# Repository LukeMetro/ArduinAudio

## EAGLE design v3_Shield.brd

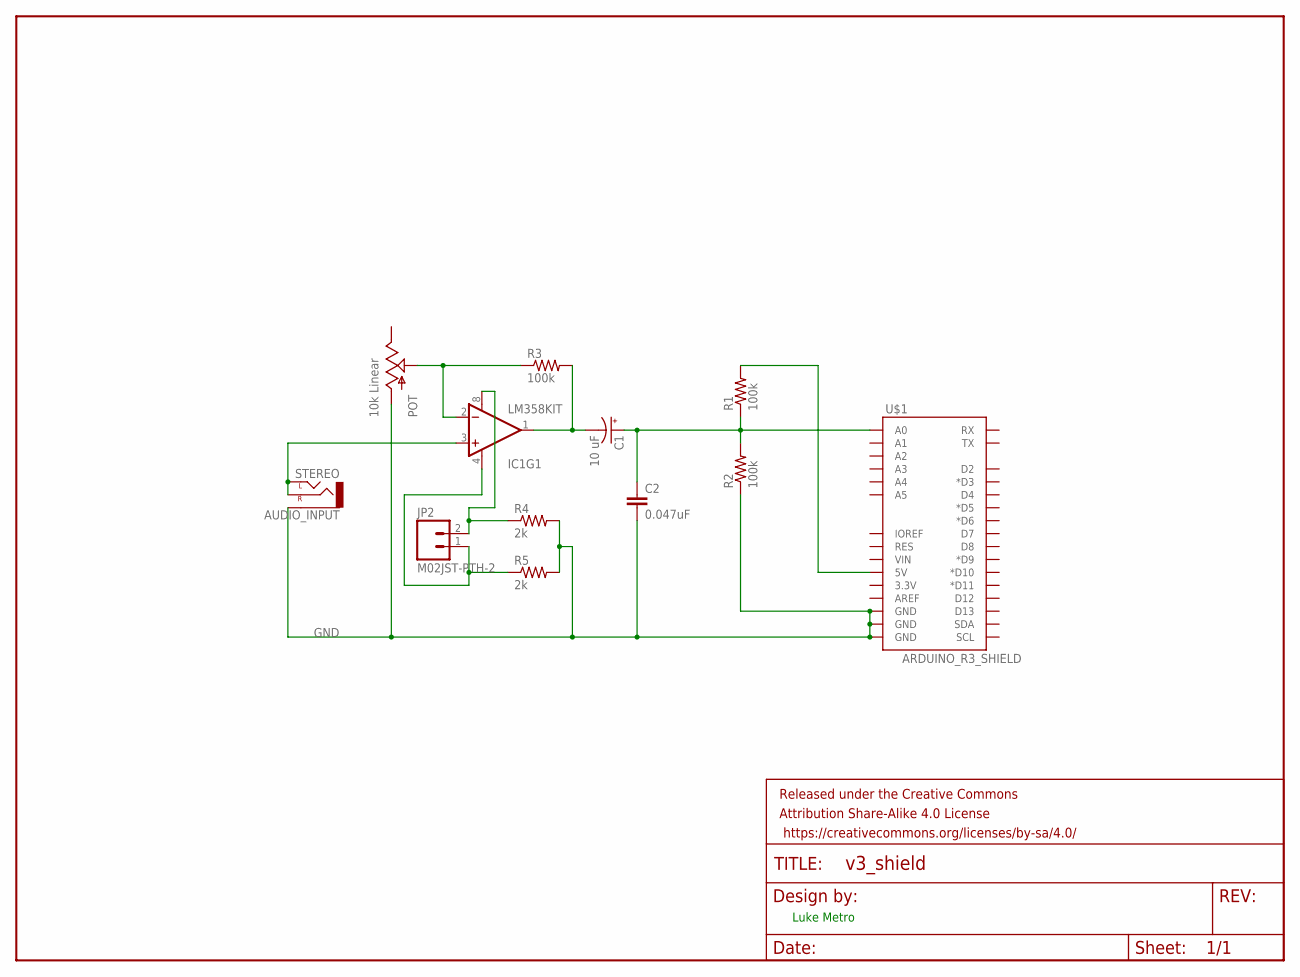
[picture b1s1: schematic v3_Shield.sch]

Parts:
AUDIO_INPUT: STEREO; AUDIO-JACK
C1: 10 uF; EIA6032
C2: 0.047uF; 0402-CAP
FRAME1: FRAME-LETTER; CREATIVE_COMMONS
IC1: LM358KIT; DIP08-KIT
JP2: M02JST-PTH-2; JST-2-PTH
POT: 10k Linear; ALPS_POT
R1, R2, R3: 100k; 0805-THM
R4, R5: 2k; 0805-THM
U$1: ARDUINO_R3_SHIELD; UNO_R3_SHIELD

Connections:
2.5V_OFFSET_HOT: R1.2, U$1.5V
GND: AUDIO_INPUT.SLEEVE, C2.2, POT.P$3 (A), R2.1, R4.2, R5.2, U$1.GND@0 (GND), U$1.GND@1 (GND), U$1.GND@2 (GND)
OPAMP_IN: AUDIO_INPUT.RING (RIGHT), AUDIO_INPUT.TIP (LEFT), IC1.3 (+IN)
OPAMP_INVERTING_INPUT: IC1.2 (-IN), POT.P$2 (S), R3.1
OPAMP_OUT: C1.P$2 (-), IC1.1 (OUT), R3.2
OPAMP_PWR_COLD: IC1.4 (V-), JP2.1, R5.1
OPAMP_PWR_HOT: IC1.8 (V+), JP2.2, R4.1
OUTPUT_SIGNAL: C1.P$1 (+), C2.1, R1.1, R2.2, U$1.A0

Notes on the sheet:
Luke Metro

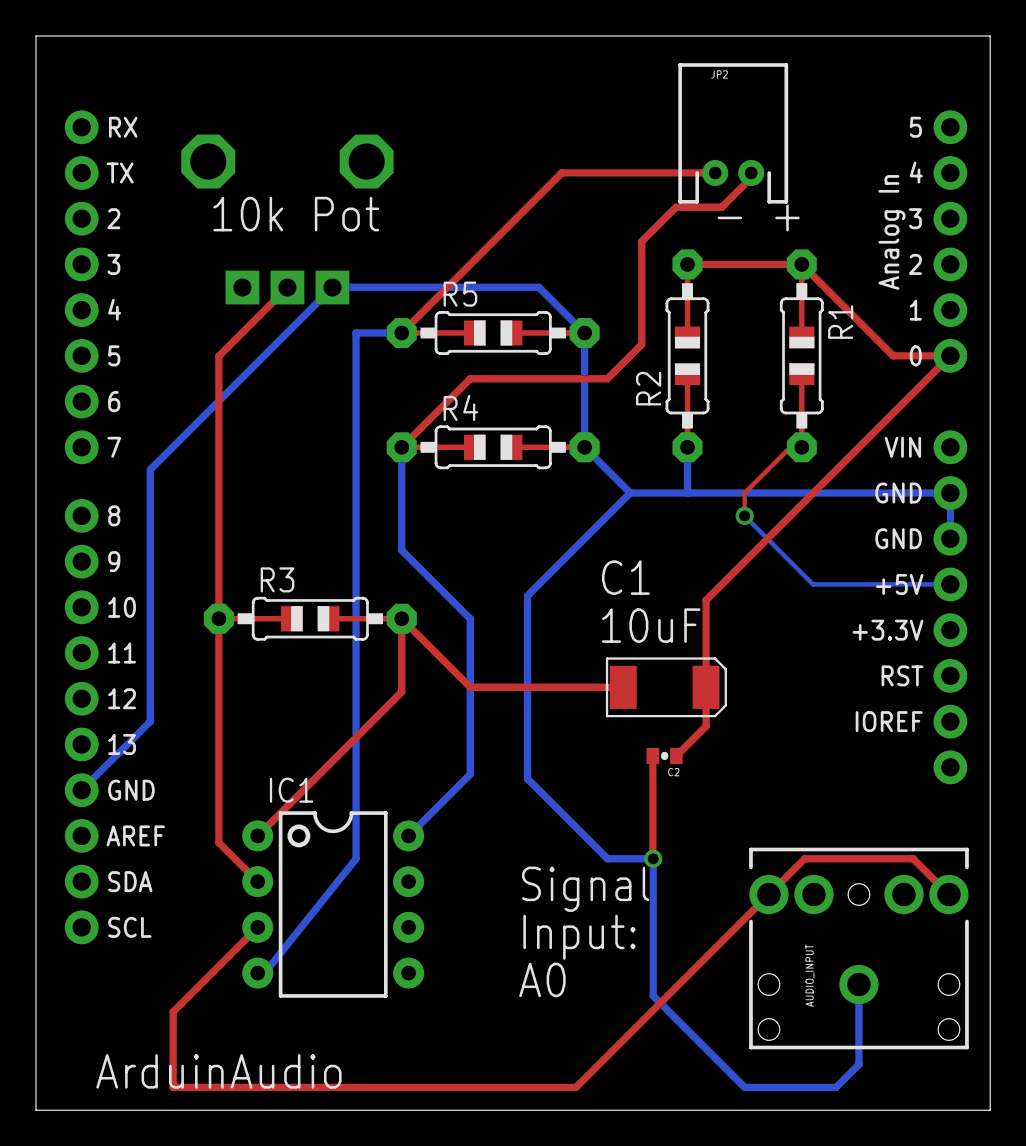
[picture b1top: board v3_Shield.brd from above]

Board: 2 copper layers, 53.0 x 59.7 mm, 13 parts (0 on the bottom side), 8 nets.

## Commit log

2014-07-13 Initial Commit
    Add all files

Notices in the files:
parts and their libraries:
SparkFun-Boards: Licensing: Creative Commons ShareAlike 4.0 International - https://creativecommons.org/licenses/by-sa/4.0
SparkFun-Aesthetics: Released under the Creative Commons Attribution Share-Alike 4.0 License
SparkFun-Aesthetics: https://creativecommons.org/licenses/by-sa/4.0
